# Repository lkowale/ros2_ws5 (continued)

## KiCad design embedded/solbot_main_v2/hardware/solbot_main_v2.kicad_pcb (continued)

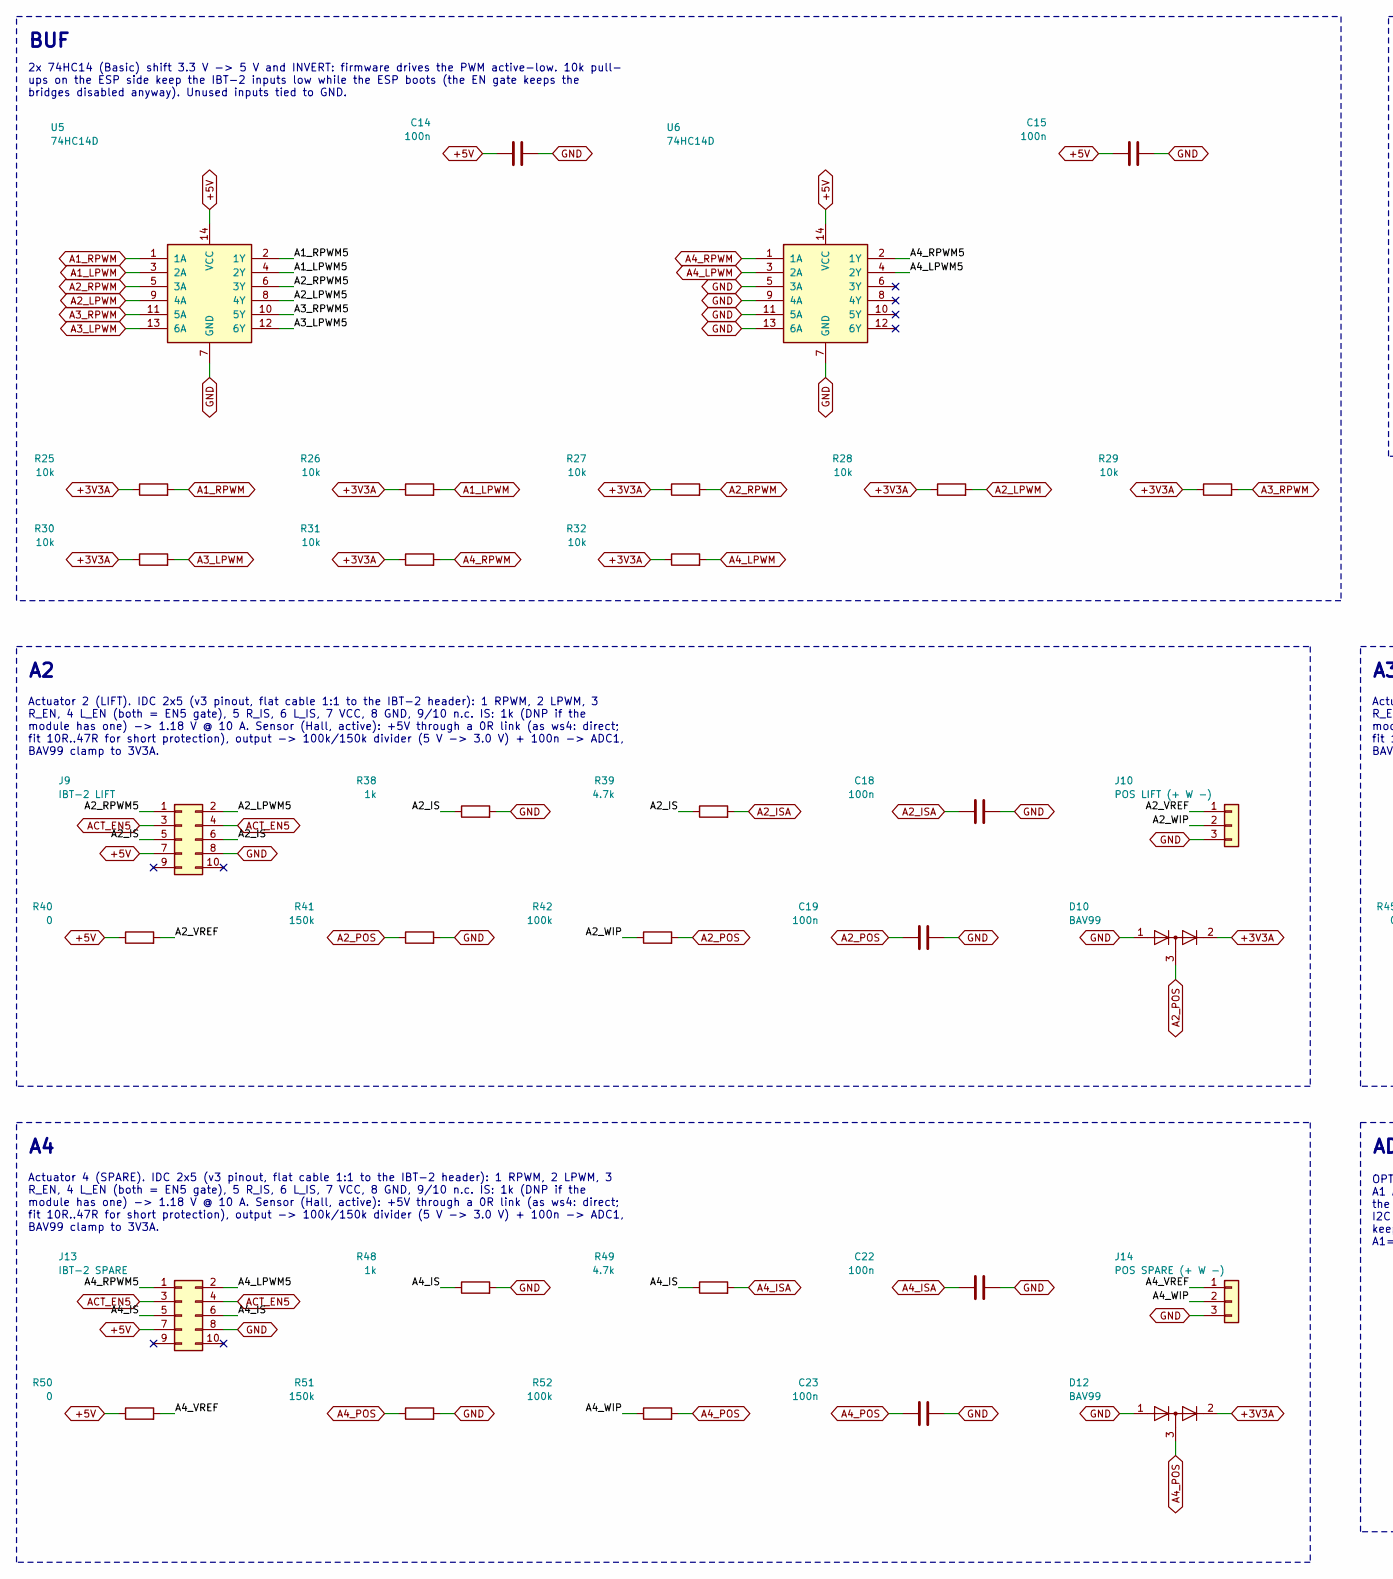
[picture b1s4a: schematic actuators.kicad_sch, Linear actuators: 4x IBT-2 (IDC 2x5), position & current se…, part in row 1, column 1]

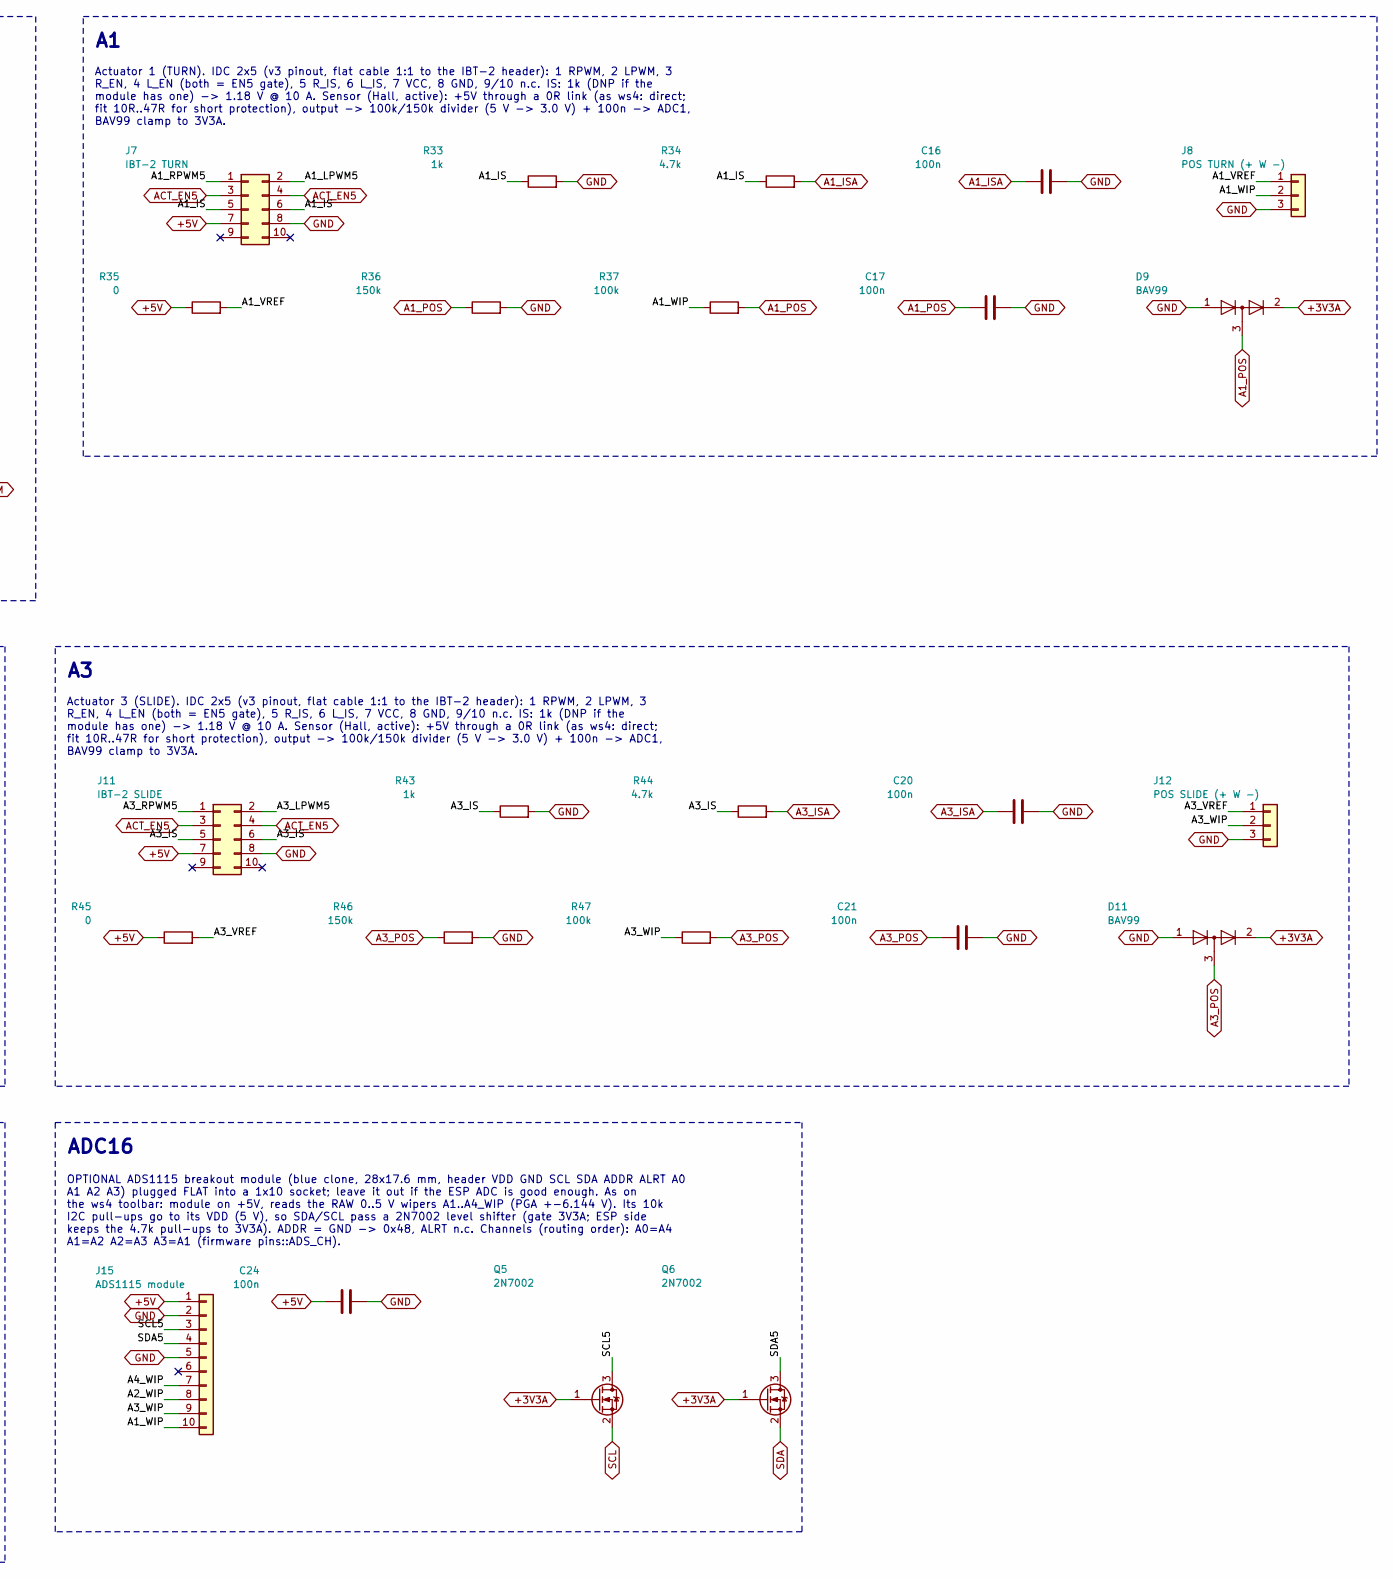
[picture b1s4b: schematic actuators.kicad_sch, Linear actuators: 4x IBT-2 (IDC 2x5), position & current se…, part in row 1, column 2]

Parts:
C14, C15, C16, C17, C18, C19, C20, C21, C22, C23, C24: 100n; C_0603_1608Metric; LCSC C14663
D9, D10, D11, D12: BAV99; SOT-23; LCSC C2500
J7: IBT-2 TURN; IDC-Header_2x05_P2.54mm_Vertical
J8: POS TURN (+ W -); TerminalBlock_Phoenix_PT-1,5-3-3.5-H_1x03_P3.50mm_Horizontal
J9: IBT-2 LIFT; IDC-Header_2x05_P2.54mm_Vertical
J10: POS LIFT (+ W -); TerminalBlock_Phoenix_PT-1,5-3-3.5-H_1x03_P3.50mm_Horizontal
J11: IBT-2 SLIDE; IDC-Header_2x05_P2.54mm_Vertical
J12: POS SLIDE (+ W -); TerminalBlock_Phoenix_PT-1,5-3-3.5-H_1x03_P3.50mm_Horizontal
J13: IBT-2 SPARE; IDC-Header_2x05_P2.54mm_Vertical
J14: POS SPARE (+ W -); TerminalBlock_Phoenix_PT-1,5-3-3.5-H_1x03_P3.50mm_Horizontal
J15: ADS1115 module; PinSocket_1x10_P2.54mm_Vertical
Q5, Q6: 2N7002; SOT-23; LCSC C8545
R25, R26, R27, R28, R29, R30, R31, R32: 10k; R_0603_1608Metric; LCSC C25804
R33, R38, R43, R48: 1k; R_0603_1608Metric; LCSC C21190
R34, R39, R44, R49: 4.7k; R_0603_1608Metric; LCSC C23162
R35, R40, R45, R50: 0; R_0603_1608Metric; LCSC C21189
R36, R41, R46, R51: 150k; R_0603_1608Metric; LCSC C22807
R37, R42, R47, R52: 100k; R_0603_1608Metric; LCSC C25803
U5, U6: 74HC14D; SOIC-14_3.9x8.7mm_P1.27mm; LCSC C5605

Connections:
+3V3A: D9.2 (A), D10.2 (A), D11.2 (A), D12.2 (A), Q5.1 (G), Q6.1 (G), R25.1, R26.1, R27.1, R28.1, R29.1, R30.1, R31.1, R32.1; also elsewhere on the board
+5V: C14.1, C15.1, C24.1, J7.7, J9.7, J11.7, J13.7, J15.1, R35.1, R40.1, R45.1, R50.1, U5.14 (VCC), U6.14 (VCC); also elsewhere on the board
A1_IS: J7.5, J7.6, R33.1, R34.1
A1_ISA: C16.1, R34.2; also elsewhere on the board
A1_LPWM: R26.2, U5.3 (2A); also elsewhere on the board
A1_LPWM5: J7.2, U5.4 (2Y)
A1_POS: C17.1, D9.3 (K), R36.1, R37.2; also elsewhere on the board
A1_RPWM: R25.2, U5.1 (1A); also elsewhere on the board
A1_RPWM5: J7.1, U5.2 (1Y)
A1_VREF: J8.1, R35.2
A1_WIP: J8.2, J15.10, R37.1
A2_IS: J9.5, J9.6, R38.1, R39.1
A2_ISA: C18.1, R39.2; also elsewhere on the board
A2_LPWM: R28.2, U5.9 (4A); also elsewhere on the board
A2_LPWM5: J9.2, U5.8 (4Y)
A2_POS: C19.1, D10.3 (K), R41.1, R42.2; also elsewhere on the board
A2_RPWM: R27.2, U5.5 (3A); also elsewhere on the board
A2_RPWM5: J9.1, U5.6 (3Y)
A2_VREF: J10.1, R40.2
A2_WIP: J10.2, J15.8, R42.1
A3_IS: J11.5, J11.6, R43.1, R44.1
A3_ISA: C20.1, R44.2; also elsewhere on the board
A3_LPWM: R30.2, U5.13 (6A); also elsewhere on the board
A3_LPWM5: J11.2, U5.12 (6Y)
A3_POS: C21.1, D11.3 (K), R46.1, R47.2; also elsewhere on the board
A3_RPWM: R29.2, U5.11 (5A); also elsewhere on the board
A3_RPWM5: J11.1, U5.10 (5Y)
A3_VREF: J12.1, R45.2
A3_WIP: J12.2, J15.9, R47.1
A4_IS: J13.5, J13.6, R48.1, R49.1
A4_ISA: C22.1, R49.2; also elsewhere on the board
A4_LPWM: R32.2, U6.3 (2A); also elsewhere on the board
A4_LPWM5: J13.2, U6.4 (2Y)
A4_POS: C23.1, D12.3 (K), R51.1, R52.2; also elsewhere on the board
A4_RPWM: R31.2, U6.1 (1A); also elsewhere on the board
A4_RPWM5: J13.1, U6.2 (1Y)
A4_VREF: J14.1, R50.2
A4_WIP: J14.2, J15.7, R52.1
ACT_EN5: J7.3, J7.4, J9.3, J9.4, J11.3, J11.4, J13.3, J13.4; also elsewhere on the board
GND: C14.2, C15.2, C16.2, C17.2, C18.2, C19.2, C20.2, C21.2, C22.2, C23.2, C24.2, D9.1 (K), D10.1 (K), D11.1 (K), D12.1 (K), J7.8, J8.3, J9.8, J10.3, J11.8, J12.3, J13.8, J14.3, J15.2, J15.5, R33.2, R36.2, R38.2, R41.2, R43.2, R46.2, R48.2, R51.2, U5.7 (GND), U6.5 (3A), U6.7 (GND), U6.9 (4A), U6.11 (5A), U6.13 (6A); also elsewhere on the board
SCL: Q5.2 (S); also elsewhere on the board
SCL5: J15.3, Q5.3 (D)
SDA: Q6.2 (S); also elsewhere on the board
SDA5: J15.4, Q6.3 (D)

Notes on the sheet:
BUF
2x 74HC14 (Basic) shift 3.3 V -> 5 V and INVERT: firmware drives the PWM active-low. 10k pull- ups on the ESP side keep the IBT-2 inputs low while the ESP boots (the EN gate keeps the bridges disabled anyway). Unused inputs tied to GND.
Actuator 1 (TURN). IDC 2x5 (v3 pinout, flat cable 1:1 to the IBT-2 header): 1 RPWM, 2 LPWM, 3 R_EN, 4 L_EN (both = EN5 gate), 5 R_IS, 6 L_IS, 7 VCC, 8 GND, 9/10 n.c. IS: 1k (DNP if the module has one) -> 1.18 V @ 10 A. Sensor (Hall, active): +5V through a 0R link (as ws4: direct; fit 10R..47R for s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
Actuator 2 (LIFT). IDC 2x5 (v3 pinout, flat cable 1:1 to the IBT-2 header): 1 RPWM, 2 LPWM, 3 R_EN, 4 L_EN (both = EN5 gate), 5 R_IS, 6 L_IS, 7 VCC, 8 GND, 9/10 n.c. IS: 1k (DNP if the module has one) -> 1.18 V @ 10 A. Sensor (Hall, active): +5V through a 0R link (as ws4: direct; fit 10R..47R for s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
Actuator 3 (SLIDE). IDC 2x5 (v3 pinout, flat cable 1:1 to the IBT-2 header): 1 RPWM, 2 LPWM, 3 R_EN, 4 L_EN (both = EN5 gate), 5 R_IS, 6 L_IS, 7 VCC, 8 GND, 9/10 n.c. IS: 1k (DNP if the module has one) -> 1.18 V @ 10 A. Sensor (Hall, active): +5V through a 0R link (as ws4: direct; fit 10R..47R for 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
Actuator 4 (SPARE). IDC 2x5 (v3 pinout, flat cable 1:1 to the IBT-2 header): 1 RPWM, 2 LPWM, 3 R_EN, 4 L_EN (both = EN5 gate), 5 R_IS, 6 L_IS, 7 VCC, 8 GND, 9/10 n.c. IS: 1k (DNP if the module has one) -> 1.18 V @ 10 A. Sensor (Hall, active): +5V through a 0R link (as ws4: direct; fit 10R..47R for 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
ADC16
OPTIONAL ADS1115 breakout module (blue clone, 28x17.6 mm, header VDD GND SCL SDA ADDR ALRT A0 A1 A2 A3) plugged FLAT into a 1x10 socket; leave it out if the ESP ADC is good enough. As on the ws4 toolbar: module on +5V, reads the RAW 0..5 V wipers A1..A4_WIP (PGA +-6.144 V). Its 10k I2C pull-ups go 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

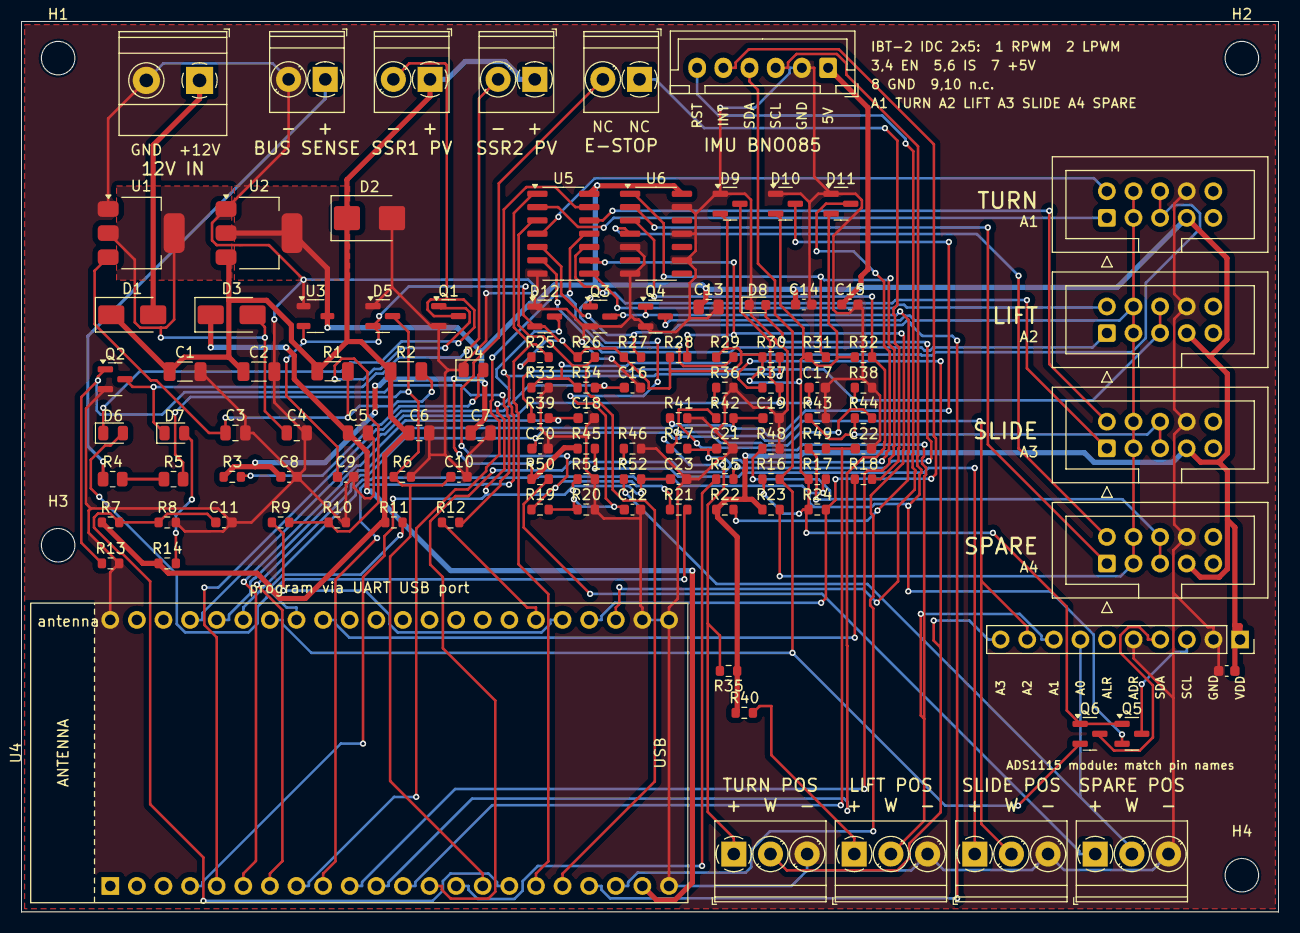
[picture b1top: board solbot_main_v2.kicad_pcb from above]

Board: 2 copper layers, 120.0 x 85.0 mm, 119 parts (0 on the bottom side), 72 nets.

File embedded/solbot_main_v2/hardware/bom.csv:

Qty,Value,Footprint,MPN / note,References
14,100n,C_0603_1608Metric,,C10 C11 C12 C14 C15 C16 C17 C18 C19 C20 C21 C22 C23 C24
4,10u 25V,C_0805_2012Metric,,C3 C5 C6 C13
2,10u 50V,C_1206_3216Metric,,C1 C2
2,1u,C_0603_1608Metric,,C8 C9
2,22u 25V,C_0805_2012Metric,,C4 C7
5,BAV99,SOT-23,,D5 D9 D10 D11 D12
1,KT-0603R red,LED_0603_1608Metric,,D8
1,KT-0805G green,LED_0805_2012Metric,,D4
2,KT-0805Y yellow,LED_0805_2012Metric,,D6 D7
1,SMBJ18A,D_SMB,,D2
2,SS34,D_SMA,,D1 D3
1,12V IN,"TerminalBlock_Phoenix_MKDS-1,5-2-5.08_1x02_P5.08mm_Horizontal",,J1
1,ADS1115 module,PinSocket_1x10_P2.54mm_Vertical,,J15
1,BUS SENSE,"TerminalBlock_Phoenix_PT-1,5-2-3.5-H_1x02_P3.50mm_Horizontal",,J2
1,E-STOP (NC loop),"TerminalBlock_Phoenix_PT-1,5-2-3.5-H_1x02_P3.50mm_Horizontal",,J5
1,IBT-2 LIFT,IDC-Header_2x05_P2.54mm_Vertical,,J9
1,IBT-2 SLIDE,IDC-Header_2x05_P2.54mm_Vertical,,J11
1,IBT-2 SPARE,IDC-Header_2x05_P2.54mm_Vertical,,J13
1,IBT-2 TURN,IDC-Header_2x05_P2.54mm_Vertical,,J7
1,IMU BNO085,JST_XH_B6B-XH-A_1x06_P2.50mm_Vertical,,J6
1,POS LIFT (+ W -),"TerminalBlock_Phoenix_PT-1,5-3-3.5-H_1x03_P3.50mm_Horizontal",,J10
1,POS SLIDE (+ W -),"TerminalBlock_Phoenix_PT-1,5-3-3.5-H_1x03_P3.50mm_Horizontal",,J12
1,POS SPARE (+ W -),"TerminalBlock_Phoenix_PT-1,5-3-3.5-H_1x03_P3.50mm_Horizontal",,J14
1,POS TURN (+ W -),"TerminalBlock_Phoenix_PT-1,5-3-3.5-H_1x03_P3.50mm_Horizontal",,J8
1,SSR1 PV (+in / -in),"TerminalBlock_Phoenix_PT-1,5-2-3.5-H_1x02_P3.50mm_Horizontal",,J3
1,SSR2 PV (+in / -in),"TerminalBlock_Phoenix_PT-1,5-2-3.5-H_1x02_P3.50mm_Horizontal",,J4
6,2N7002,SOT-23,,Q1 Q2 Q3 Q4 Q5 Q6
4,0,R_0603_1608Metric,,R35 R40 R45 R50
2,100,R_0603_1608Metric,,R9 R12
8,100k,R_0603_1608Metric,,R7 R10 R13 R20 R37 R42 R47 R52
12,10k,R_0603_1608Metric,,R8 R21 R22 R24 R25 R26 R27 R28 R29 R30 R31 R32
4,150k,R_0603_1608Metric,,R36 R41 R46 R51
6,1k,R_0603_1608Metric,,R15 R19 R33 R38 R43 R48
2,2.2k,R_0603_1608Metric,,R3 R23
2,22R 0.25W,R_1206_3216Metric,,R1 R2
1,30k,R_0603_1608Metric,,R6
8,4.7k,R_0603_1608Metric,,R11 R14 R16 R17 R34 R39 R44 R49
1,470,R_0603_1608Metric,,R18
2,470k 150V,R_0805_2012Metric,,R4 R5
2,74HC14D,SOIC-14_3.9x8.7mm_P1.27mm,,U5 U6
2,AMS1117-5.0,SOT-223-3_TabPin2,,U1 U2
1,ESP32-S3-DevKitC-1,ESP32-S3-DevKitC-1_Socket,,U4
1,XC6206P332MR-G,SOT-23-3,,U3

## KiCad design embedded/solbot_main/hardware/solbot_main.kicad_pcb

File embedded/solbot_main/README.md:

# solbot_main v4 — ESP32-S3 main controller

> **⚠️ Superseded — do not order this board.** The board to order is `../solbot_main_v2`
> (compact, JLC Basic parts, ready to order). This v1 board (190 × 155 mm, on-board 4-pack
> power path) is kept as a reference design only. Its parts were never mapped to JLC numbers.

Successor of the v3 board (`ros2_ws4/embedded/main_esp32_pio`, EasyEDA schematic
`Schematic_solbo3_2026-10-15/esp32.svg`). One board that

* manages power: up to **4 battery packs (10S … 20S)** + **PV input**, each with
  voltage & bidirectional current measurement and its own switch; PV charging control
* drives **6 linear actuators** through external **IBT-2 (BTS7960)** modules, closed loop
  on potentiometer feedback, with per-actuator current sensing
  (A1 steering, A2 tool lift, A3 tool-bar slider, A4–A6 spare)
* reads the **BNO085** IMU
* talks MQTT over WiFi, with the same topics and payloads as v3

```
embedded/solbot_main/
├── hardware/               KiCad 7 project (generated, then editable in KiCad)
│   ├── solbot_main.kicad_pro / .kicad_sch (+4 sub-sheets) / .kicad_pcb
│   ├── lib/                ESP32-S3-DevKitC-1 symbol + socket footprint
│   ├── bom.csv
│   └── gen/                Python generators (design.py = single source of truth)
└── firmware/               PlatformIO (ESP32-S3, Arduino)
    └── test/host/          host unit tests for actuator + power logic
```

## Hardware

### Block diagram

```
 BAT1+ ─[1mΩ]─┬─[Q◄►Q]─┐            BUS+ ──► loads (drive, 12 V DC-DC, lasers…)
 BAT2+ ─[1mΩ]─┼─[Q◄►Q]─┤
 BAT3+ ─[1mΩ]─┼─[Q◄►Q]─┼── BUS+ ── 2×100 µF, TVS, divider
 BAT4+ ─[1mΩ]─┼─[Q◄►Q]─┤
 PV+   ─[1mΩ]─┼─[Q◄►Q]─┘            each channel: INA241A2 (I) + 1031k/33k divider (V)
              │
              └─ES1D─► VAUX (diode-OR of all inputs) ─► LM5164 ─► +5V ─► AP2112 ─► +3V3A
                                                               └► AP2112 ─► +3V3_POT (pots)
 ESP32-S3-DevKitC-1
   I2C-A: BNO085, ADS1115 0x48/0x49 (6 pot positions, VREF, 5V)
   I2C-B: ADS1115 0x48/0x49/0x4A (pack/PV/bus V+I, temp), TCA9535 (pack switches)
   MCPWM 12 ch ─► 74HCT244 (5 V, /OE = E-stop gate) ─► 6× IBT-2 header
   ADC1 ×6 ◄── IBT-2 R_IS‖L_IS (1 kΩ)
```

### Design decisions

| Topic | Choice | Why |
|---|---|---|
| Pack/PV switch | Back-to-back P-FETs, SQM120P10_10M1L (−100 V, 10 mΩ, D2PAK), high side | blocks current in both directions, pack negatives stay on common GND, simple gate drive |
| Gate drive | MMBTA42 current sink (~2 mA) + 12 V zener + 10 k | Vgs = −12 V **independent of bus voltage**, so the same circuit covers 10S and 20S |
| Current sense | 1 mΩ Kelvin shunt (WSK2512) + **INA241A2** (20 V/V, −5…110 V CM, REF = Vs/2) | bidirectional (charge/discharge), ±82 A range, 6 mA/LSB at the ADS1115 |
| Voltage sense | 2×499 k (1206) + 33 k 0.1 % → ADS1115 | 3.2 V at 100 V; measured on the pack side, so the pack voltage is visible with the switch open |
| Logic supply | diode-OR of all inputs → **LM5164** (6–100 V) → 5 V | the controller never browns out, whichever packs are switched off; RON/FB/Type-3 ripple values computed from the LM5164 datasheet (SNVSAU4D eq. 15, 24–26) |
| Switch latch | **TCA9535** (no internal pull-ups) drives pack switches | outputs survive ESP32 reset/OTA (firmware adopts the latched state); power-on default = all packs off |
| PV switch | direct GPIO40, same switch circuit | fast cut-off on reverse current / over-voltage |
| Actuator outputs | MCPWM (2 units × 3 operators = 12 outputs) → 74HCT244 | ESP32-S3 has only 8 LEDC channels; 3.3 V is out of spec for the 74HC244 on the IBT-2 module |
| E-stop | GPIO39 → NC loop → 2N7002 → 74HCT244 /OE, outputs pulled down | an open loop, a missing jumper or an un-booted ESP32 all leave the IBT-2s disabled, in hardware |
| Pot excitation | own AP2112 (+3V3_POT), 47 Ω per connector, ratiometric (VREF measured) | a shorted sensor cable can't take down the ADC/I2C rail |
| Wiper inputs | 4.7 k + 100 n + BAT54S clamp, 1 M pull-down | survive miswiring; an open wiper reads 0, so the firmware raises a SENSOR fault |
| Two I2C buses | IMU + actuator ADCs on A, power on B | BNO085 clock-stretch problems can't stall power management; resolves the BNO085/ADS 0x4A address clash |

### GPIO map (ESP32-S3-DevKitC-1)

| Function | GPIO |
|---|---|
| IBT-2 IS (ADC1) A1…A6 | 1, 2, 4, 5, 6, 7 |
| RPWM/LPWM A1 / A2 / A3 | 9/10, 11/12, 13/14 |
| RPWM/LPWM A4 / A5 / A6 | 15/16, 17/18, 21/47 |
| I2C-A SDA/SCL | 41 / 42 |
| I2C-B SDA/SCL | 19 / 20 (native USB port unusable; program via the **UART** USB port) |
| ACT_EN / ESTOP_SENSE | 39 / 8 |
| PV_EN | 40 |
| IMU_INT / LED_ERR | 3 / 46 |
| left free | 0, 35–37 (PSRAM on R8 modules), 38/48 (on-board RGB LED), 43/44 (UART0), 45 |

TCA9535 (0x20): P00–P03 = BAT1–4_EN, P04 = IMU_RST, P05 = PWR LED, P06–P17 → `EXP IO` header.

### Connectors

| Ref | What | Pinout |
|---|---|---|
| BAT1–4+, PV+, BUS+ ×2, GND ×3 | M4 ring-terminal lugs | — |
| IBT-2 #1–#6 | 1×8 pin header, 1:1 with the IBT-2 header (straight Dupont cable) | RPWM LPWM R_EN L_EN R_IS L_IS VCC(5 V) GND |
| POS 1–6 | 3-pin 3.5 mm screw terminal | +3V3_POT, wiper, GND |
| IMU BNO085 | JST-XH 6 | 5V GND SCL SDA INT RST |
| E-STOP | 2-pin 3.5 mm screw terminal | NC contact loop (fit a wire bridge if no E-stop is used) |
| I2C-B ext | JST-XH 4 | 3V3 GND SDA SCL |
| EXP IO | 1×12 header | 3V3 GND IO0…IO9 |

### PCB

190 × 155 mm, 2 layers, **2 oz copper** (required). The high-current path per channel is a
straight column (lug → shunt → FET → FET → bus bar) of locked wide tracks on both layers.
The bus bar is 8 mm wide on both layers, stitched with vias. Both layers carry GND pours.
Signals were autorouted with FreeRouting; see "Status" below.

Regenerate:
```sh
cd hardware/gen
python3 build.py                                   # schematic, project, BOM
env -i PATH=/usr/bin:/bin HOME=$HOME python3 gen_pcb.py place     # board + DSN
(cd .. && env -i PATH=/usr/bin:/bin HOME=$HOME timeout 2700 \
   java -jar freerouting-2.0.1.jar -de solbot_main.dsn -do solbot_main.ses -mt 4 --gui.enabled=false)
env -i PATH=/usr/bin:/bin HOME=$HOME python3 gen_pcb.py finish    # import SES, pours, DRC
```
FreeRouting 2.0.1 is the newest release that runs on Java 21. It ignores its pass limit
and only stops when everything is routed, so run it under `timeout`. The committed
`solbot_main.ses` converged after 45 passes (about 30 min).
(`env -i` is needed inside the VS Code snap, whose libraries break KiCad/Java.)
Once you start editing the PCB by hand in KiCad, stop re-running `gen_pcb.py place`,
because it rebuilds the board from scratch. Schematic edits can still go through
`design.py` + `build.py`, followed by *Update PCB from Schematic* (UUIDs are stable).

## Firmware

```sh
cd firmware
pio run -e solbot_main -t upload          # via the UART USB port
OTA_HOST=<ip> pio run -e solbot_main_ota -t upload
test/host/run.sh                          # host unit tests (after one `pio run`)
```

Tasks: **control** at 50 Hz (bus A: BNO085 drained between ADC conversions, positions,
IS currents, PWM), **power** at 10 Hz (bus B: 12 ADC channels, policy,
break-before-make switch writes), **loop()** for WiFi/MQTT/OTA/telemetry. The control
loops never depend on the network.

### MQTT API

Unchanged from v3 (ROS `steering.py`, `imu_bridge.py`, `esp32_power_monitor.py` keep working):

| Topic | Dir | Payload |
|---|---|---|
| `steer_position` | sub | `{"data": legacy}`. Legacy counts are the old ADS1015 scale, so `steering.yaml` stays valid |
| `lift/set_position` | sub | `{"data": legacy}` |
| `motor_direction` | sub | toggles the steering direction |
| `ads` | pub 10 Hz | `WAS, WAS_pwm, WAS_pos_goal, LAS, LAS_pwm, LAS_pos_goal` (+ new `TBS`, `TBS_goal`, `estop`) |
| `imu` | pub 5 Hz | `orientation[4], heading_accuracy, angular_velocity[3], linear_acceleration[3]` |
| `esp32/power` | pub 1 Hz | `voltage, pv_on` (+ `bus_v, load_i, temp_c, pv{…}, packs[{id,v,i,on,mode,soc,ah_out,ah_in,fault}]`) |
| `esp32/diag` | pub | loop gaps, E-stop events |
| `<dev>/config`, `get_config`, `enter_ap` | sub | as before (`config_status` now also contains actuator and power configs) |

New:

| Topic | Payload |
|---|---|
| `slider/set_position` / `slider/position` | `{"data": metres}` (tool-bar slider, ±0.10 m after calibration) |
| `<dev>/act/<1-6\|name>/set` | `{"pos": units}` or `{"raw": legacy}` or `{"ratio": 0..1}` |
| `<dev>/act/<1-6\|name>/config` | partial update of `name, enabled, invert, r_min, r_max, u_min, u_max, deadband, slow_zone, pwm_min, pwm_max, pwm_slew, i_limit, oc_ms, stall_delta, stall_ms, cmd_timeout_ms, sensor_check` (saved to NVS) |
| `<dev>/act/reset`, `<dev>/act/enable {"data":0/1}` | clear faults / software enable |
| `<dev>/act/state` (pub 5 Hz) | per-actuator `pos, goal, ratio, duty, amps, fault` |
| `<dev>/power/cmd` | `{"pack":2,"mode":"auto\|on\|off"}`, `{"pv":"auto\|on\|off"}`, `{"reset_faults":true}` |
| `<dev>/power/config` | partial update of `cells[4], cap_ah[4], v_chg, v_chg_hyst, v_ov, v_uv, v_uv_reconnect, v_crit, dv_par, i_dis_max, i_chg_max, i_pv_max, smart_swap, v_scale[6], …` |
| `<dev>/settings` | `{"imu_hz": 5, "ads_hz": 10}` |

`<dev>` defaults to `ESP32_solbot_main`.

### Power policy (auto mode)

* **Discharge:** the highest pack anchors the bus. Other packs join only when their
  open-circuit voltage (V + I·R_int) is within `dv_par` × cells (0.3 V at 10S) of the
  bus, so packs are never paralleled across a large voltage step.
* **Charging:** the PV switch closes when the PV voltage exceeds the bus voltage and every
  connected pack is below `cells × (v_chg − v_chg_hyst)`. It opens at `cells × v_chg`, on
  reverse current (sun gone), or on charge over-current. Defaults reproduce v3 at 10S:
  off at 41.0 V, back on below 40.0 V, with a 30 s minimum off-time.
* **Protection:** discharge over-current (30 A) and charge over-current (15 A) per pack,
  pack over-voltage (stops PV), under-voltage disconnect after 5 s (the last pack stays
  connected until `v_crit`), and board over-temperature (stops PV).
* **Smart swap** (off by default): when PV has had a surplus of more than 2 A for 60 s,
  the bus is moved onto a lower pack that couldn't join, so PV energy goes into the
  emptiest pack.
* Every switch change is **break-before-make** (3 ms).

### Calibration (once per robot)

1. Voltage: compare `packs[].v` with a multimeter and set `power/config {"v_scale":[…]}`
   (BAT1–4, PV, BUS).
2. Actuators: jog to each mechanical end with `act/<n>/set {"ratio":…}`, read `ratio`
   from `act/state`, then set `r_min/r_max` a little inside the ends, plus `u_min/u_max`
   in your units. Steering and lift default to legacy counts; the slider defaults to
   −0.10…+0.10 m.
3. Direction: if an actuator runs away from its goal, set `{"invert":true}`.
4. Current-sense zero needs nothing: the firmware auto-zeroes each channel while its switch
   is open.

## Status / check before ordering

* Schematic: generated; KiCad's netlist matches `design.py` node-for-node (166 nets).
* Firmware: builds (RAM 17 %, flash 26 %), and the host logic tests pass
  (they were mutation-checked). **It hasn't run on hardware yet.**
* PCB: fully routed. DRC finds 0 unconnected items, 0 clearance errors and 0 shorts.
  The remaining entries are silkscreen warnings, plus `lib_footprint_issues`, which only
  appear in the headless run (`KICAD7_FOOTPRINT_DIR` unset). Gerbers, drill and
  placement files are in `hardware/fab/`, and the schematic PDF is
  `hardware/solbot_main_schematic.pdf`. The signal routing is autorouted, so look it over
  in KiCad before ordering. Copper-to-edge clearance is 0.3 mm (within JLCPCB's limits).
* **Verify:** the ESP32-S3-DevKitC-1 header row spacing on your actual module. The
  footprint uses 25.4 mm (third-party CAD models), but Espressif's own footprint says
  22.86 mm. Measure it.
* **Verify:** whether your IBT-2 modules already have an IS resistor. If they do, don't
  fit the 1 k R_IS resistors (A*_IS to GND).
* **For 20S:** the FETs are −100 V parts, so keep PV Voc ≤ 90 V and change the TVS from
  SMCJ58A to SMCJ85A. Set `cells` to 20.
* Pack fuses are **not** on the board. Fit one per pack, close to the pack.
* Inrush: the first pack switches on in about 0.5 ms (slow gate charge), which acts as a
  soft start for the board's 200 µF. If the loads on BUS+ add several mF (motor
  controllers), give them their own precharge, or check the SQM120P10 SOA for ½·C·V².
* LM5164 component values follow the datasheet equations. Cross-check them in TI
  WEBENCH (VIN 18–100 V, 5 V / 1 A).

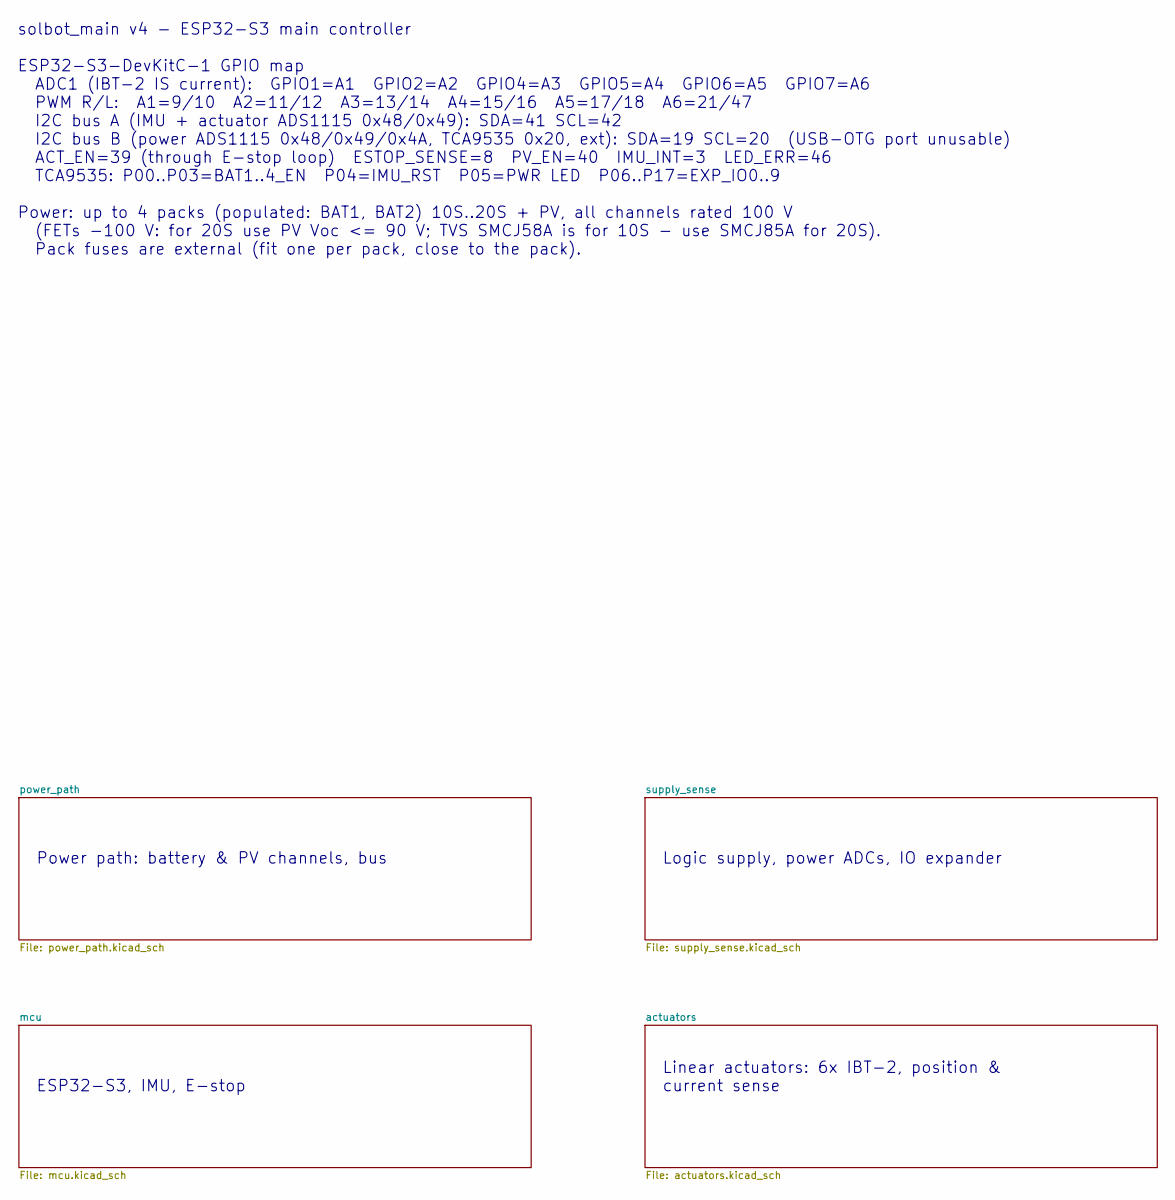
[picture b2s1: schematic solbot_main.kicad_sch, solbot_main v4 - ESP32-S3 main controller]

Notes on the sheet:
solbot_main v4 - ESP32-S3 main controller ESP32-S3-DevKitC-1 GPIO map ADC1 (IBT-2 IS current): GPIO1=A1 GPIO2=A2 GPIO4=A3 GPIO5=A4 GPIO6=A5 GPIO7=A6 PWM R/L: A1=9/10 A2=11/12 A3=13/14 A4=15/16 A5=17/18 A6=21/47 I2C bus A (IMU + actuator ADS1115 0x48/0x49): SDA=41 SCL=42 I2C bus B (power ADS1115 0x4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
Power path: battery & PV channels, bus
Logic supply, power ADCs, IO expander
ESP32-S3, IMU, E-stop
Linear actuators: 6x IBT-2, position & current sense
